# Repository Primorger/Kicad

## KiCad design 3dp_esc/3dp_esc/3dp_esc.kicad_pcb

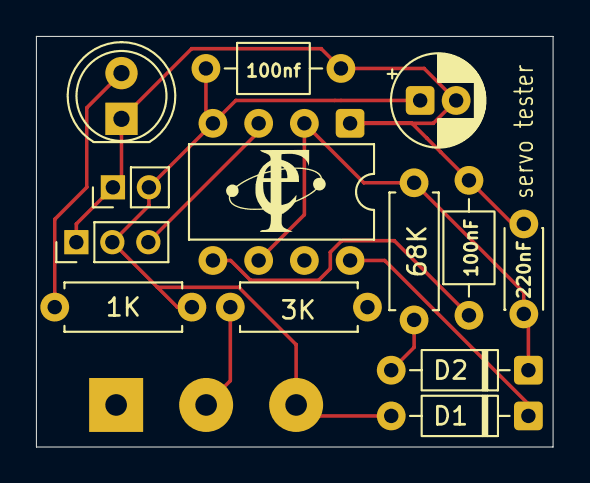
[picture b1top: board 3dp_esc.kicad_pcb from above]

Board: 2 copper layers, 28.7 x 22.8 mm, 14 parts (0 on the bottom side), 9 nets.

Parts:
1K, 3K, 68K: R; R_Axial_DIN0207_L6.3mm_D2.5mm_P7.62mm_Horizontal
1uF1: C_Polarized; CP_Radial_D5.0mm_P2.00mm
10K1: R_Potentiometer; Potentiometer_Alps_RK163_Single_Horizontal
100nF, 100nf: C; C_Axial_L3.8mm_D2.6mm_P7.50mm_Horizontal
220nF: C; C_Disc_D4.3mm_W1.9mm_P5.00mm
D1, D2: 1N4148; D_DO-35_SOD27_P7.62mm_Horizontal
D3: LD271; LED_D5.0mm_Clear
J1: Conn_01x03_Pin; PinHeader_1x03_P2.00mm_Vertical
J2: Conn_01x02_Pin; PinHeader_1x02_P2.00mm_Vertical
U1: NE555P; DIP-8_W7.62mm

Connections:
+: 1K.1, 1uF1.1, 10K1.3, 100nf.1, D1.2 (A), J1.2, J2.2, U1.4 (~RST)
-5.6V Bat: 1uF1.2, 100nF.2, 100nf.2, 220nF.2, D3.1 (K), J1.1, J2.1, U1.1 (GND)
unnamed: 3K.1, 10K1.2
unnamed: D1.1 (K), U1.8 (VCC)
unnamed: 3K.2, 68K.1, D2.2 (A), U1.7 (DISCH)
unnamed: 68K.2, 220nF.1, D2.1 (K), U1.2 (TRIG), U1.6 (THRES)
unnamed: 1K.2, D3.2 (A)
unnamed: 100nF.1, U1.5 (CONT)
signal: J1.3, U1.3 (OUT)

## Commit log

2026-03-20 Servo tester added
2026-03-20 pin headers added
2026-03-20 Footprints added
2026-03-20 footprints added
    footprints added
2026-03-20 nets created
2026-03-20 PCB done, waiting for feedback!
2026-04-04 pinheadersfixed
2026-04-04 i hope its fixed (it isn't)
2026-04-08 this is good
